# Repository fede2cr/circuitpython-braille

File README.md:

# circuitpython-braille
Braille Keyboard made in [CircuitPython](https://circuitpython.org/)

This is a keyboard for writing in Braille. This type of keyboards are used for transcribing books and letters to braille punched paper books for hand reading, and is an important tool for making reading material inclusive.

## Using via serial console

If you prefer, we can start with the Keyboard emulation turned off, by moving the switch no the CircuitPlayground Express to the Off position.

Now, get a serial console to read the output of the program. Please have in mind that the mu-editor [does not print unicode characters properly](https://github.com/mu-editor/mu/issues/797) so the braille character will not print properly.

## Using via keyboard emulation

To practice, get a text editor with a new document, and turn on keyboard emulation by making sure that the switch on the CircuitPlayground Express is set to On.

## How to write Braille

Get a braille table, from [the code](https://github.com/fede2cr/circuitpython-braille/blob/master/braille.py), from [Wikipedia](https://en.wikipedia.org/wiki/Braille) or from a [book](https://www.amazon.com/gp/product/1539368130/).

The easiest is the letter A. Just touch the pad labeled A1, and that is it.

For the letter B, press at the same time pad A1 and pad A2.

Letter C is **not** A1+A2+A3, but is actually just A1 with A4.

Now, how about trying to write your name using the table as reference?

## TODO

- Add support for "indicators", used in numbers, uppercase and others.
- Custom designed PCB for easy fabrication

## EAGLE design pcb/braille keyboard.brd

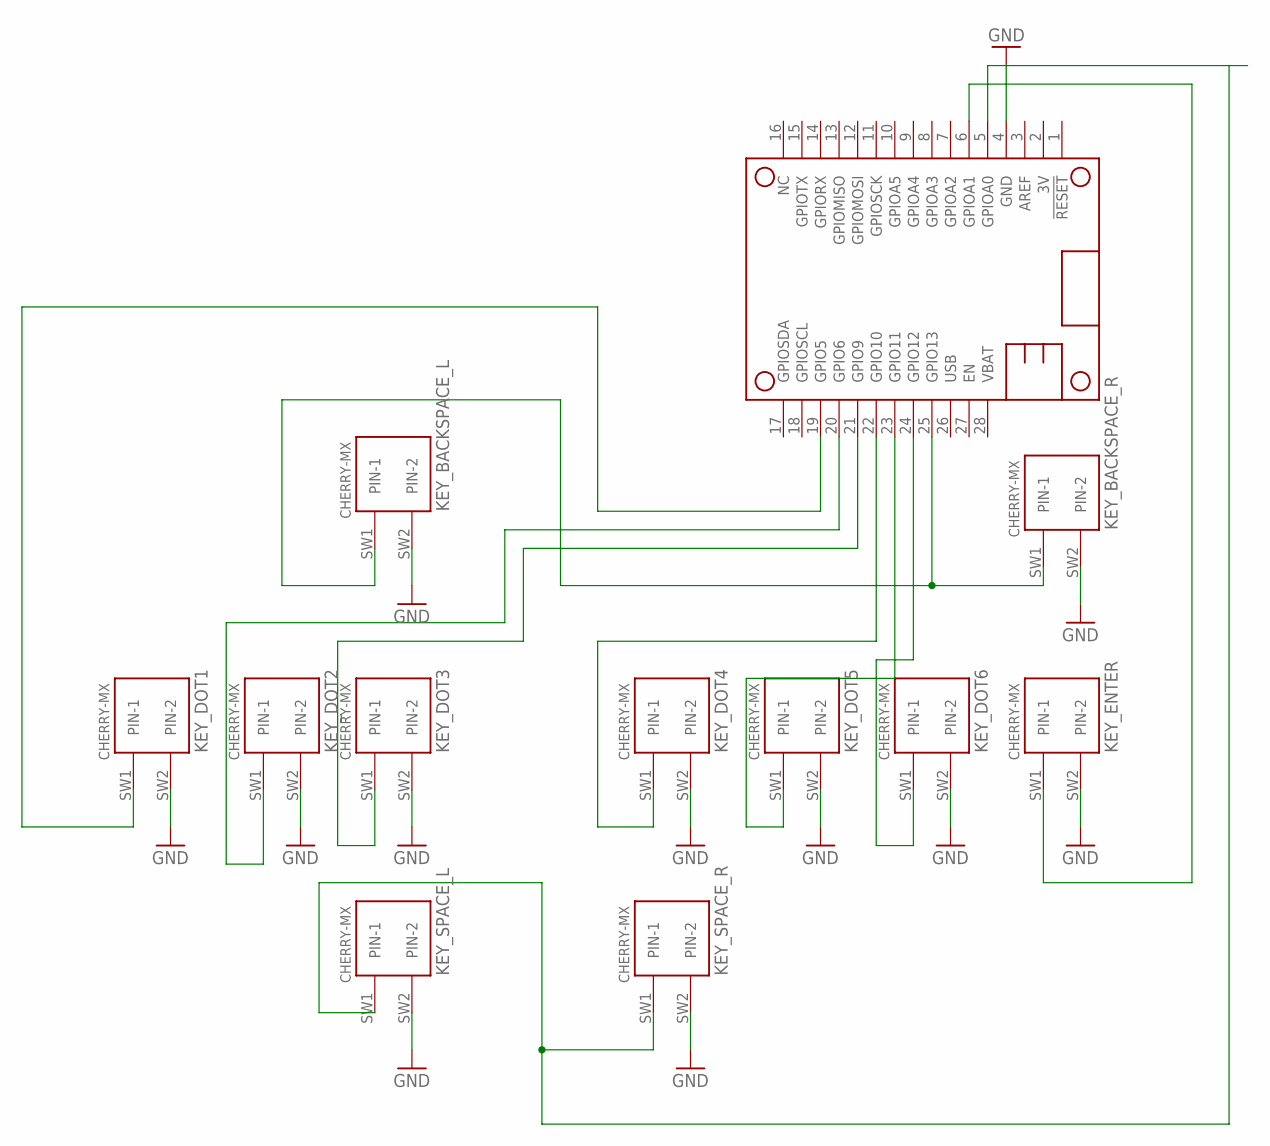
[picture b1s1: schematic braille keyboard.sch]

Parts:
KEY_BACKSPACE_L: CHERRY-MX
KEY_BACKSPACE_R: CHERRY-MX
KEY_DOT1, KEY_DOT2, KEY_DOT3, KEY_DOT4, KEY_DOT5, KEY_DOT6: CHERRY-MX
KEY_ENTER: CHERRY-MX
KEY_SPACE_L: CHERRY-MX
KEY_SPACE_R: CHERRY-MX
MS1: FEATHERWING

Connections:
GND: KEY_BACKSPACE_L.SW2 (PIN-2), KEY_BACKSPACE_R.SW2 (PIN-2), KEY_DOT1.SW2 (PIN-2), KEY_DOT2.SW2 (PIN-2), KEY_DOT3.SW2 (PIN-2), KEY_DOT4.SW2 (PIN-2), KEY_DOT5.SW2 (PIN-2), KEY_DOT6.SW2 (PIN-2), KEY_ENTER.SW2 (PIN-2), KEY_SPACE_L.SW2 (PIN-2), KEY_SPACE_R.SW2 (PIN-2), MS1.4 (GND)
unnamed: KEY_DOT1.SW1 (PIN-1), MS1.19 (GPIO5)
unnamed: KEY_DOT2.SW1 (PIN-1), MS1.20 (GPIO6)
unnamed: KEY_DOT3.SW1 (PIN-1), MS1.21 (GPIO9)
unnamed: KEY_SPACE_L.SW1 (PIN-1), KEY_SPACE_R.SW1 (PIN-1), MS1.5 (GPIOA0)
unnamed: KEY_DOT4.SW1 (PIN-1), MS1.22 (GPIO10)
unnamed: KEY_DOT5.SW1 (PIN-1), MS1.23 (GPIO11)
unnamed: KEY_DOT6.SW1 (PIN-1), MS1.24 (GPIO12)
unnamed: KEY_BACKSPACE_L.SW1 (PIN-1), KEY_BACKSPACE_R.SW1 (PIN-1), MS1.25 (GPIO13)
unnamed: KEY_ENTER.SW1 (PIN-1), MS1.6 (GPIOA1)

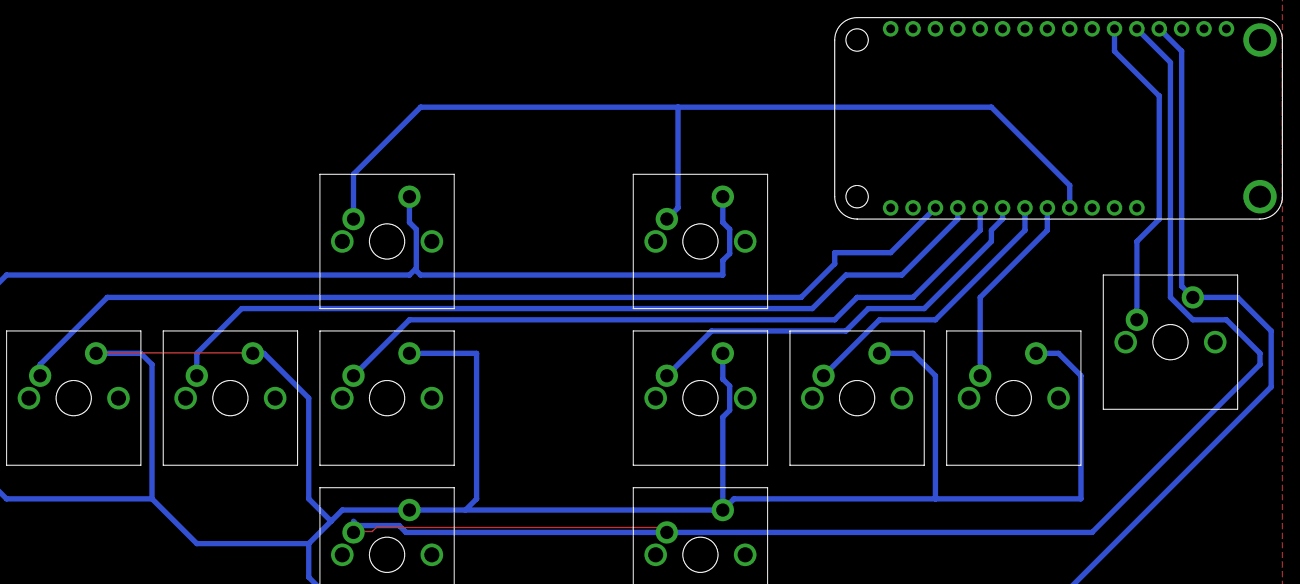
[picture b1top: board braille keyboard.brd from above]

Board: 2 copper layers, 12 parts (0 on the bottom side), 10 nets.

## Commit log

2019-03-21 Adding layout and measurements for braille parts
2019-03-21 Correct layout for keyboard
2019-03-22 Adding basic keyboard library
2019-08-16 Moving to dictionary
2019-08-16 Adding to-braille, code cleanup
2019-08-16 Adding HID support
2019-08-16 Adding CPX image, CC by Kattni
2019-08-16 Improving README
2019-08-19 Moving to nested dictionary, adding indicators and simple
2019-08-19 Moves alphabet to separate file, inicial try to debounce, adding more braille cells and indicators
2019-08-19 Testing debouncer, code cleanup to use cpx library
2019-08-19 Adding small tone when dots are recognized
2019-08-19 Erasing tasks from TODO in README
2019-08-19 Adding space and enter. Moving bit table to 8 bits. Adding enter+space to README
2019-08-23 Adding mechanical keyboard switch version, backspace works!
2019-08-26 Adding video for ItsyBitsy version
2019-08-26 Fixing typos in README
2019-10-10 Moviendo version de touch afuera, actualizando README
2019-10-10 Minor changes to README
2019-10-29 Adding pcb, and keyboard layout
